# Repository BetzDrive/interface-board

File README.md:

# Interface Board

This board is intended to connect a chain of 48 VDC RS-485 motor controllers to
the outside world.

## Features

 * USB - RS485 conversion. This is accomplished via the [FT232H](https://www.ftdichip.com/Products/ICs/FT232H.htm) and [ADM2682E](https://www.analog.com/en/products/adm2682e.html)
 IC's. The combination of these chips should provide full electrical isolation
 to the USB host and allow ~10 Mbps throughput to/from RS485.

 * Input power sanitizing. A [LM5066](https://www.ti.com/product/LM5066)
 hotswap controller IC provides sane controlled voltage ramps when the device
 is hot-plugged, and cuts power to the system when it exceeds ~56 volts. An
 input TVS diode starts kicks in around 65 V.

 * Backdrive surge supressing. Sometimes when motors are aggressively
 backdriven by an external power source, significant voltages are generated
 "back" onto the motor bus. The board is equipped to detect this condition and
 dump power through a 10-ohm power resistor. Hysteresis and timing is provided
 by a STM32L071 microcontroller.

## Resources

 * [Schematics in PDF](hardware/blue_interface_board.pdf)
 * KiCAD design files are found in [`hardware`](hardware)
 * fabrication files for rev.A are found in [`hardware/fab`](hardware/fab)

## Renderings

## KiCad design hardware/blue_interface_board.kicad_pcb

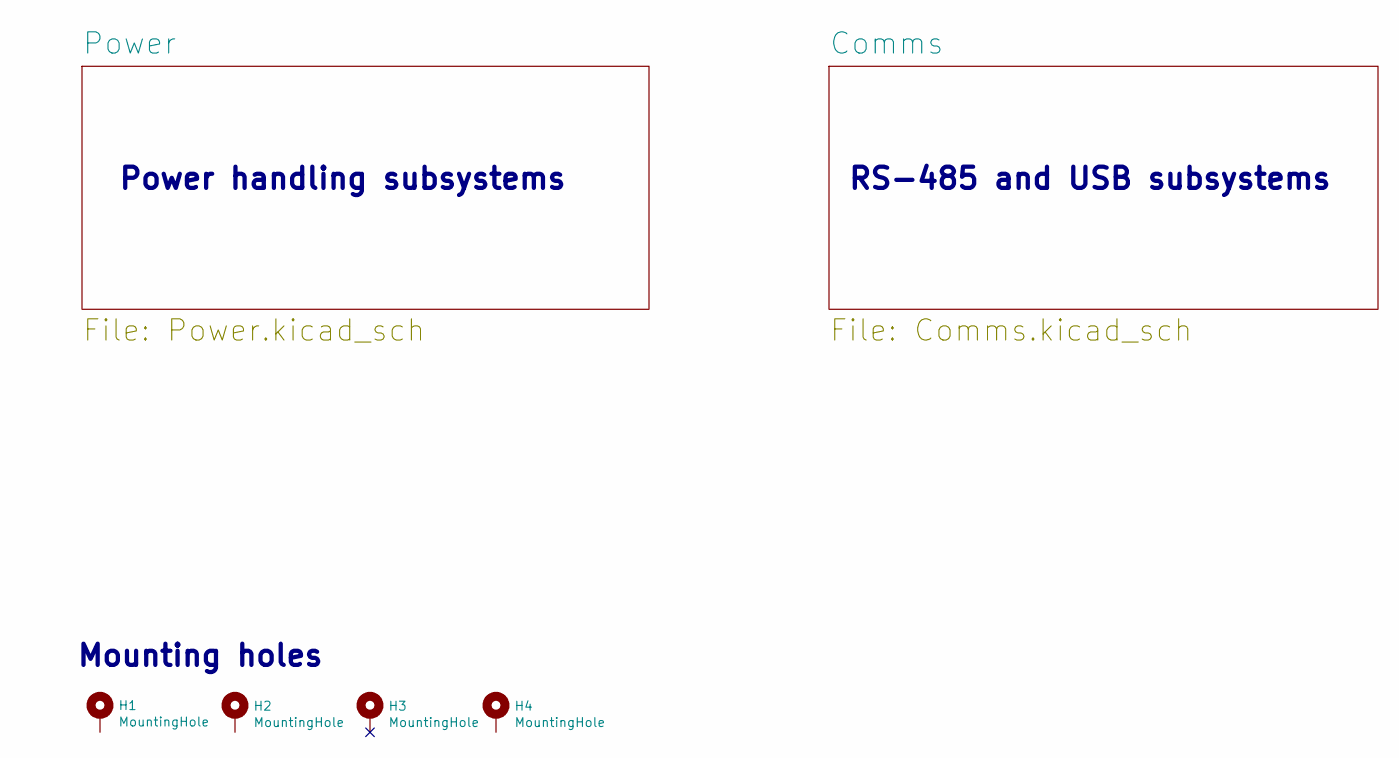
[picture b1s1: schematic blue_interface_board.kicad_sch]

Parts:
H1, H2, H3, H4: MountingHole; MountingHole_3.2mm_M3_DIN965_Pad

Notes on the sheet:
Mounting holes
Power handling subsystems
RS-485 and USB subsystems

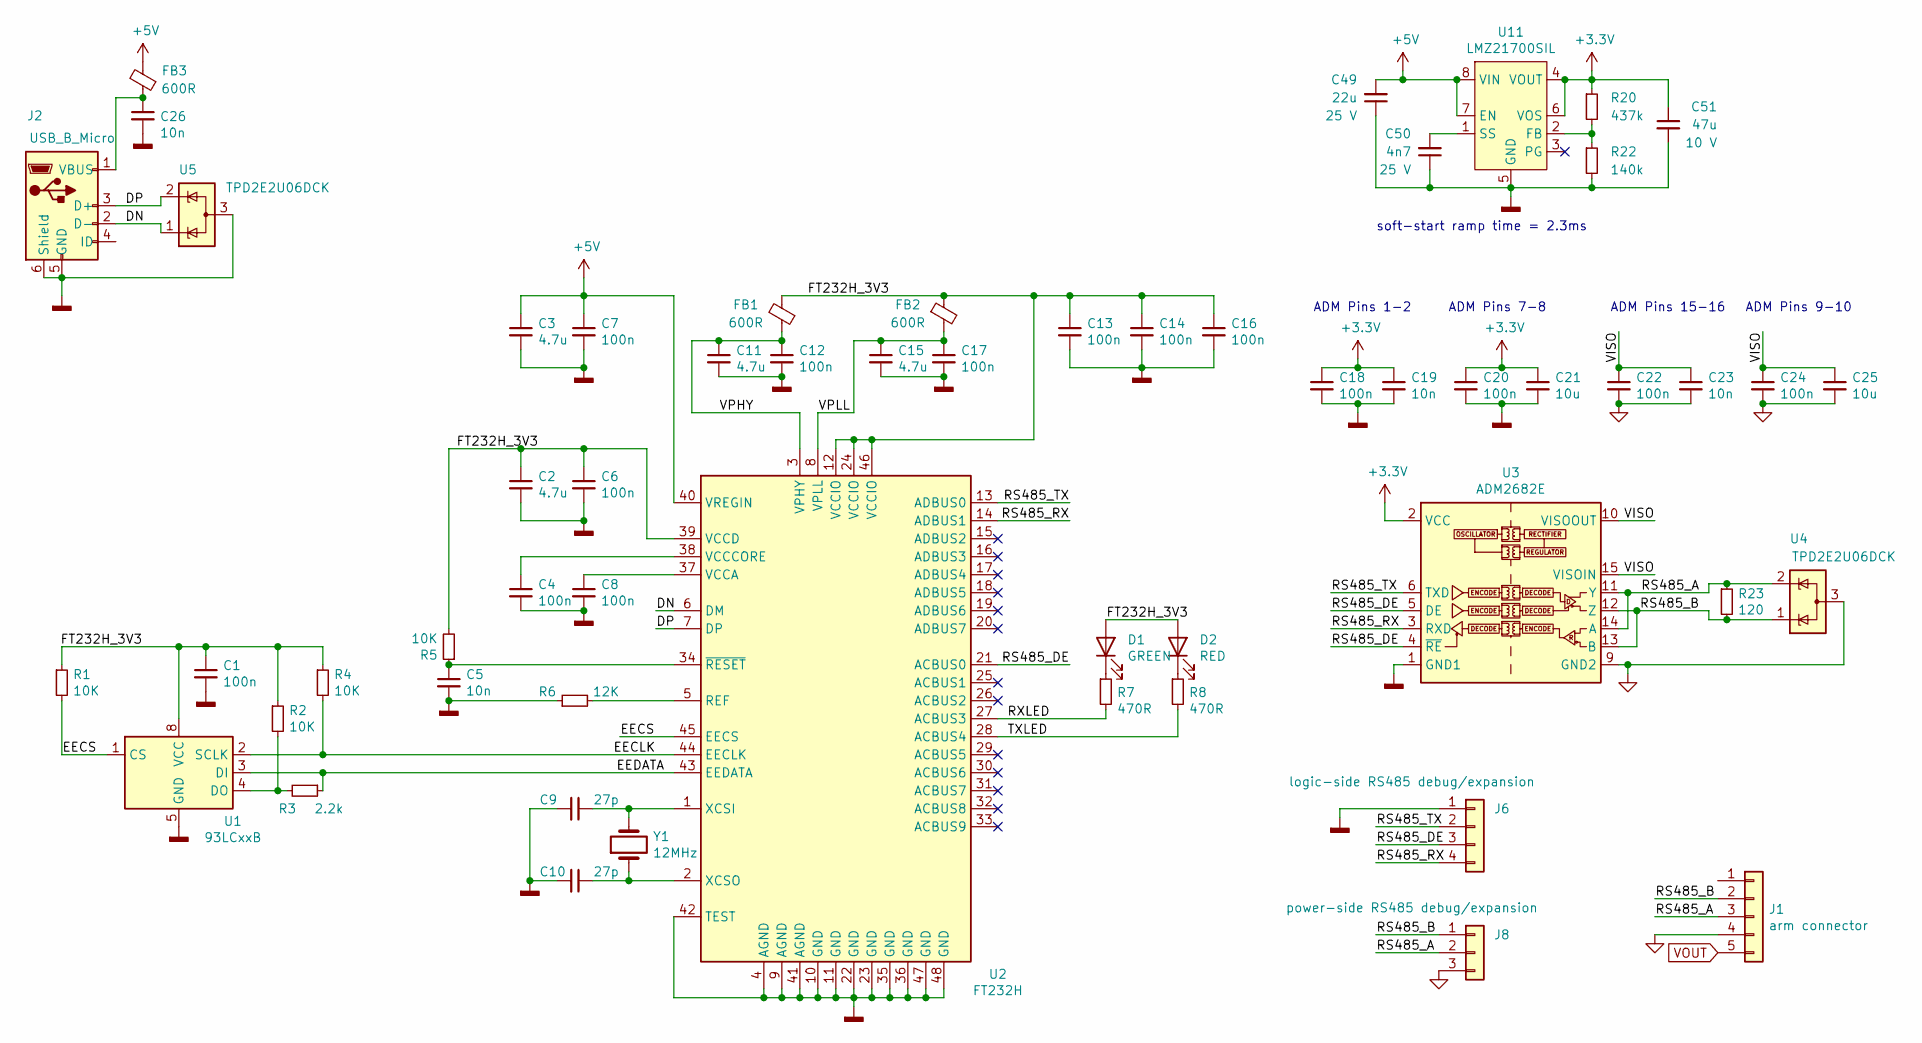
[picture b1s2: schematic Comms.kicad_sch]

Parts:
C1, C4, C6, C7, C8, C12, C13, C14, C16, C17, C18, C20, C22, C24: 100n; C_0603_1608Metric; MPN CC0603KRX7R9BB104
C2, C3, C11, C15: 4.7u; C_0603_1608Metric; Maximum Voltage 10 V; Tolerance 10%; MPN LMK107BJ475KA-T
C5, C19, C23, C26: 10n; C_0603_1608Metric; MPN CC0603KPX7R9BB103
C9, C10: 27p; C_0603_1608Metric; MPN CC0603JRNPO9BN270
C21, C25: 10u; C_0603_1608Metric; MPN GRM188R61A106KE69J
C49: 22u; C_1206_3216Metric; Maximum Voltage 25 V; Tolerance 10%; MPN CL31A226KAHNNNE
C50: 4n7; C_0603_1608Metric; Maximum Voltage 25 V; Tolerance 10%; MPN CC0603KRX7R0BB472
C51: 47u; C_1206_3216Metric; Maximum Voltage 10 V; Tolerance 10%; MPN GRM31CR61A476ME15L
D1: GREEN; LED_0603_1608Metric; MPN 150060VS75000
D2: RED; LED_0603_1608Metric; MPN 150060RS75000
FB1, FB2, FB3: 600R; R_0603_1608Metric; MPN 742792651
J1: arm connector; molex-436500511; MPN 436500510
J2: USB_B_Micro; USB_Micro-B_Wuerth_629105150521_CircularHoles; MPN 629105150521
J6: logic-side RS485 debug/expansion; PinHeader_1x04_P2.54mm_Vertical; MPN DNP
J8: power-side RS485 debug/expansion; PinHeader_1x03_P2.54mm_Vertical; MPN DNP
R1, R2, R4, R5: 10K; R_0603_1608Metric; MPN RC0603JR-0710KL
R3: 2.2k; R_0603_1608Metric; Tolerance 1%; MPN RC0603FR-072K2L
R6: 12K; R_0603_1608Metric; Tolerance 0.1%; MPN ERA-3AEB123V
R7, R8: 470R; R_0603_1608Metric; Tolerance 1%; MPN RC0603FR-07470RL
R20: 437k; R_0603_1608Metric; Tolerance 1%; MPN RC0603FR-07432KL
R22: 140k; R_0603_1608Metric; Tolerance 0.1%; MPN ERA-3AEB1403V
R23: 120; R_0603_1608Metric; Tolerance 1%; MPN RC0603FR-07120RL
U1: 93LCxxB; SOIC-8_3.9x4.9mm_P1.27mm; MPN 93LC56B/SN
U2: FT232H; LQFP-48_7x7mm_P0.5mm; MPN FT232HL-REEL
U3: ADM2682E; SOIC-16W_7.5x12.8mm_P1.27mm; MPN ADM2682EBRIZ
U4, U5: TPD2E2U06DCK; SOT-323_SC-70; MPN TPD2E2U06DCKR
U11: LMZ21700SIL; SIL0008E; MPN LMZ21700SILR
Y1: 12MHz; Crystal_SMD_5032-2Pin_5.0x3.2mm; MPN CX5032GB12000H0HPQZ1

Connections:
+3V3: C18.1, C19.1, C20.1, C21.1, C51.1, R20.1, U3.2 (VCC), U3.7 (VCC), U11.4 (VOUT), U11.6 (VOS)
+5V: C3.1, C7.1, C49.2, FB3.2, U2.40 (VREGIN), U11.7 (EN), U11.8 (VIN)
/Comms/DN: J2.2 (D-), U2.6 (DM), U5.1 (K)
/Comms/DP: J2.3 (D+), U2.7 (DP), U5.2 (K)
/Comms/EECLK: R4.2, U1.2 (SCLK), U2.44 (EECLK)
/Comms/EECS: R1.2, U1.1 (CS), U2.45 (EECS)
/Comms/EEDATA: R3.1, U1.3 (DI), U2.43 (EEDATA)
/Comms/FT232H_3V3: C1.1, C2.1, C6.1, C13.1, C14.1, C16.1, D1.2 (A), D2.2 (A), FB1.2, FB2.1, R1.1, R2.1, R4.1, R5.2, U1.8 (VCC), U2.12 (VCCIO), U2.24 (VCCIO), U2.39 (VCCD), U2.46 (VCCIO)
/Comms/RS485_A: J1.3, J8.2, R23.1, U3.11 (Y), U3.14 (A), U4.2 (K)
/Comms/RS485_B: J1.2, J8.1, R23.2, U3.12 (Z), U3.13 (B), U4.1 (K)
/Comms/RS485_DE: J6.3, U2.21 (ACBUS0), U3.4 (~RE), U3.5 (DE)
/Comms/RS485_RX: J6.4, U2.14 (ADBUS1), U3.3 (RXD)
/Comms/RS485_TX: J6.2, U2.13 (ADBUS0), U3.6 (TXD)
/Comms/RXLED: R7.2, U2.27 (ACBUS3)
/Comms/TXLED: R8.2, U2.28 (ACBUS4)
/Comms/VISO: C22.1, C23.1, C24.1, C25.1, U3.10 (VISOOUT), U3.15 (VISOIN)
/Comms/VPHY: C11.1, C12.1, FB1.1, U2.3 (VPHY)
/Comms/VPLL: C15.1, C17.1, FB2.2, U2.8 (VPLL)
GND: C22.2, C23.2, C24.2, C25.2, J1.4, J8.3, U3.9 (GND2), U3.16 (GND2), U4.3 (A); also elsewhere on the board
GNDD: C1.2, C2.2, C3.2, C4.2, C5.2, C6.2, C7.2, C8.2, C9.2, C10.2, C11.2, C12.2, C13.2, C14.2, C15.2, C16.2, C17.2, C18.2, C19.2, C20.2, C21.2, C26.2, C49.1, C50.1, C51.2, J2.5 (GND), J2.6 (Shield), J6.1, R6.1, R22.2, U1.5 (GND), U2.4 (AGND), U2.9 (AGND), U2.10 (GND), U2.11 (GND), U2.22 (GND), U2.23 (GND), U2.35 (GND), U2.36 (GND), U2.41 (AGND), U2.42 (TEST), U2.47 (GND), U2.48 (GND), U3.1 (GND1), U3.8 (GND1), U5.3 (A), U11.5 (GND), U11.9 (PAD)
unnamed: C4.1, U2.38 (VCCCORE)
unnamed: C5.1, R5.1, U2.34 (~RESET)
unnamed: C8.1, U2.37 (VCCA)
unnamed: C9.1, U2.1 (XCSI), Y1.2
unnamed: C10.1, U2.2 (XCSO), Y1.1
unnamed: C26.1, FB3.1, J2.1 (VBUS)
unnamed: C50.2, U11.1 (SS)
unnamed: D1.1 (K), R7.1
unnamed: D2.1 (K), R8.1
unnamed: R2.2, R3.2, U1.4 (DO)
unnamed: R6.2, U2.5 (REF)
unnamed: R20.2, R22.1, U11.2 (FB)
VOUT: J1.5; also elsewhere on the board

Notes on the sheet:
ADM Pins 1-2
soft-start ramp time = 2.3ms
ADM Pins 7-8
ADM Pins 15-16
ADM Pins 9-10

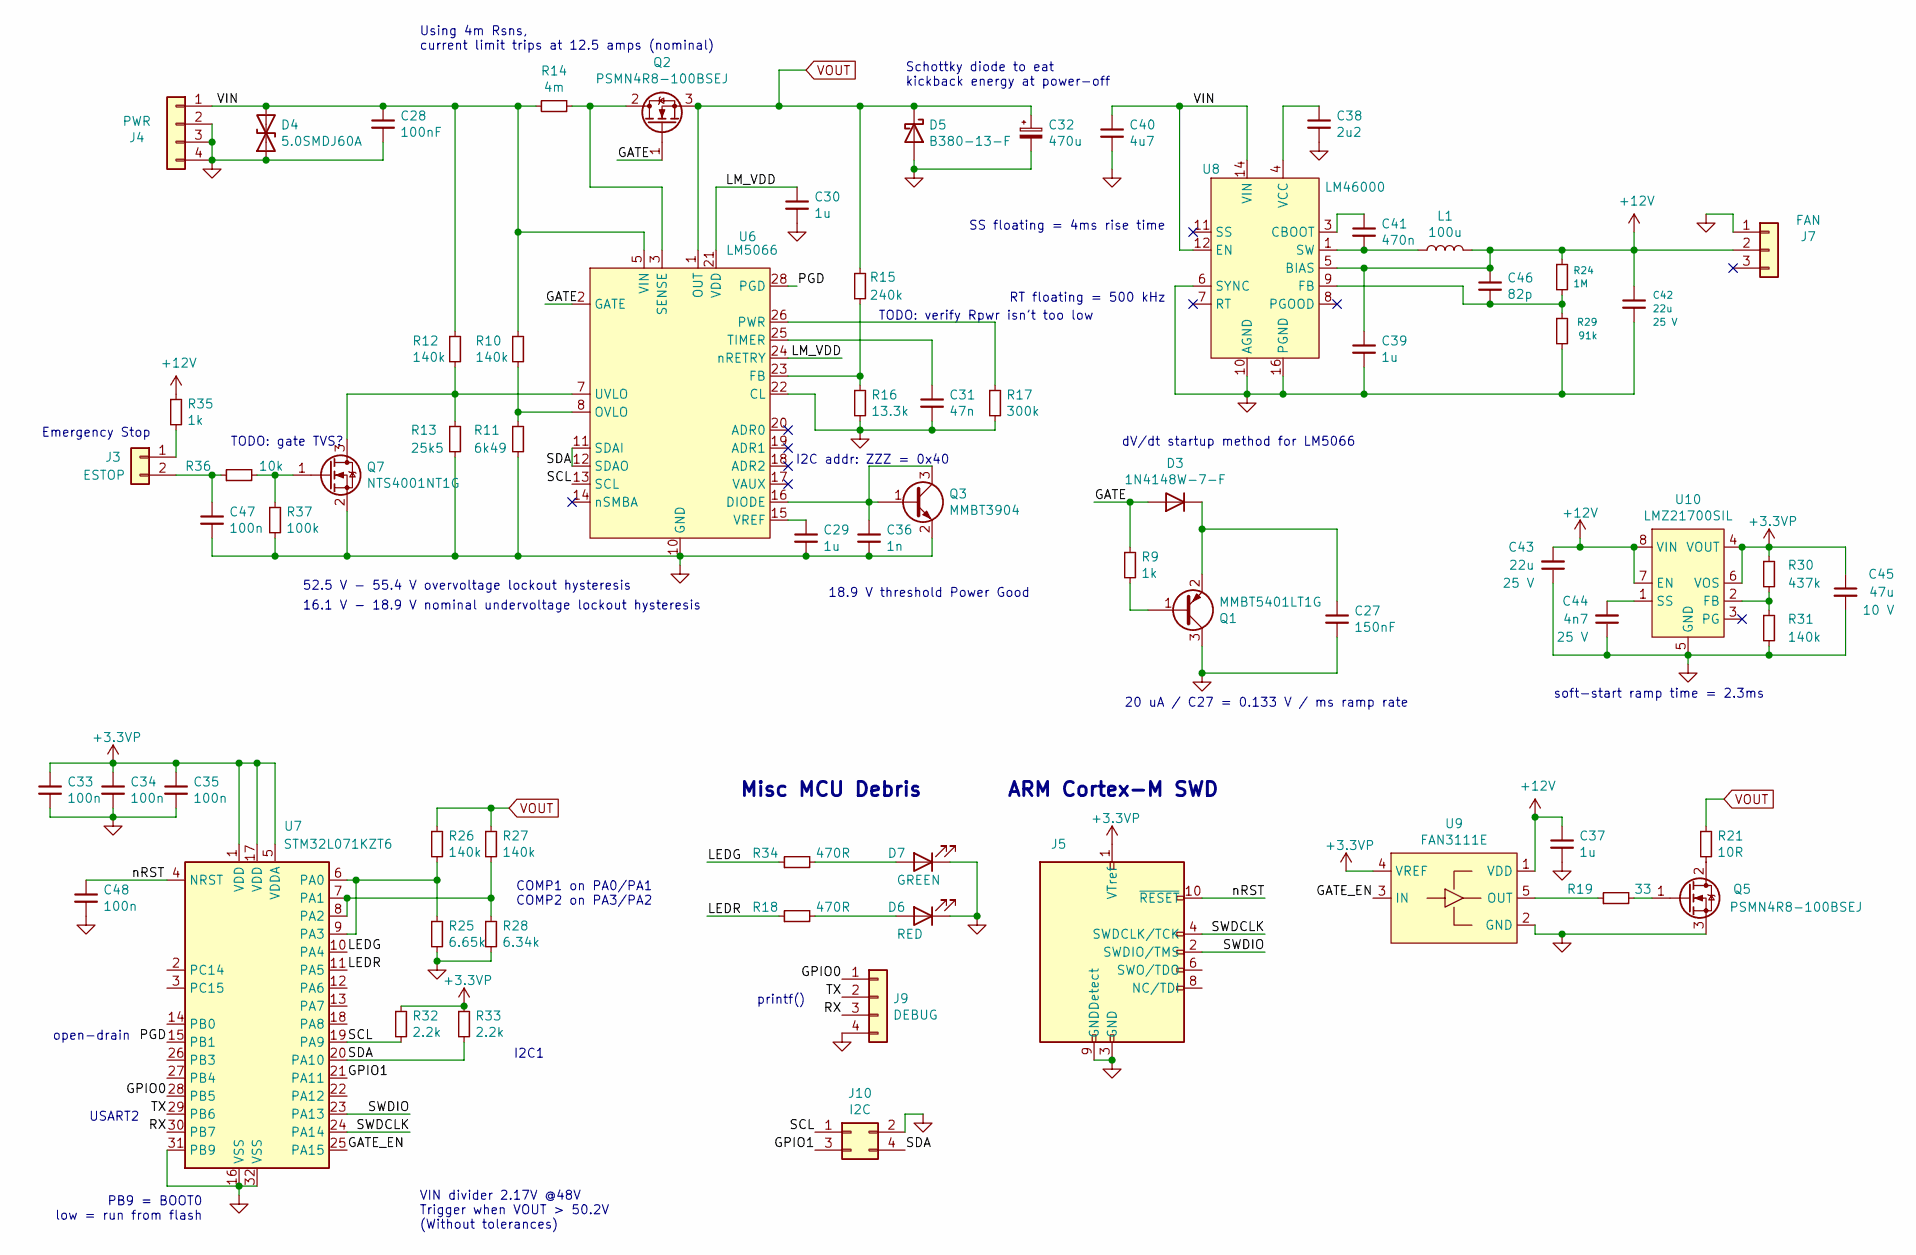
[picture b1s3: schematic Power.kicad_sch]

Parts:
C27: 150nF; C_1206_3216Metric; Maximum Voltage 250 V; Tolerance 10%; MPN C1206C154KARACAUTO
C28: 100nF; C_1206_3216Metric; Maximum Voltage 100 V; Tolerance 10%; MPN 12061C104KAT2A
C29, C30, C37, C39: 1u; C_0603_1608Metric; MPN CC0603KRX5R8BB105
C31: 47n; C_0603_1608Metric; MPN CL10B473JB8NNNC
C32: 470u; CP_Elec_18x17.5; Maximum Voltage 80 V; Tolerance 20%; MPN EEE-FK1K471AM
C33, C34, C35, C47, C48: 100n; C_0603_1608Metric; MPN CC0603KRX7R9BB104
C36: 1n; C_0603_1608Metric; MPN CC0603KRX7R9BB102
C38: 2u2; C_0603_1608Metric; Maximum Voltage 10 V; Tolerance 10%; MPN CC0603KRX5R6BB225
C40: 4u7; C_1206_3216Metric; Maximum Voltage 100 V; Tolerance 10%; MPN GRM31CC72A475KE11L
C41: 470n; C_0603_1608Metric; Maximum Voltage 25 V; Tolerance 10%; MPN CC0603KRX5R8BB474
C42, C43: 22u; C_1206_3216Metric; Maximum Voltage 25 V; Tolerance 10%; MPN CL31A226KAHNNNE
C44: 4n7; C_0603_1608Metric; Maximum Voltage 25 V; Tolerance 10%; MPN CC0603KRX7R0BB472
C45: 47u; C_1206_3216Metric; Maximum Voltage 10 V; Tolerance 10%; MPN GRM31CR61A476ME15L
C46: 82p; C_0603_1608Metric; Maximum Voltage 100 V; Tolerance 5%; MPN CL10C820JC81PNC
D3: 1N4148W-7-F; D_SOD-123; MPN 1N4148W-7-F
D4: 5.0SMDJ60A; D_SMC; MPN 5.0SMDJ60A
D5: B380-13-F; D_SMC; MPN B380-13-F
D6: RED; LED_0603_1608Metric; MPN 150060RS75000
D7: GREEN; LED_0603_1608Metric; MPN 150060VS75000
J3: ESTOP; Molex_Nano-Fit_105313-xx02_1x02_P2.50mm_Horizontal; MPN 1053131302
J4: PWR; molex-0436500213; MPN 436500214
J5: Conn_ARM_JTAG_SWD_10; PinHeader_2x05_P1.27mm_Vertical; MPN GRPB052VWVN-RC
J7: FAN; Molex_KK-254_AE-6410-03A_1x03_P2.54mm_Vertical; MPN 22232031
J9: DEBUG; PinHeader_1x04_P2.54mm_Vertical; MPN DNP
J10: I2C; PinHeader_2x02_P2.54mm_Vertical; MPN DNP
L1: 100u; L_7.3x7.3_H4.5; MPN 744777920
Q1: MMBT5401LT1G; SOT-23; MPN MMBT5401LT1G
Q2, Q5: PSMN4R8-100BSEJ; TO-263-2; MPN PSMN4R8-100BSEJ
Q3: MMBT3904; SOT-23; MPN MMBT3904-7-F
Q7: NTS4001NT1G; SOT-323_SC-70; MPN NTS4001NT1G
R9, R35: 1k; R_0603_1608Metric; Tolerance 1%; MPN RC0603FR-071KL
R10, R12, R26, R27, R31: 140k; R_0603_1608Metric; Tolerance 0.1%; MPN ERA-3AEB1403V
R11: 6k49; R_0603_1608Metric; Tolerance 0.1%; MPN ERA-3AEB6491V
R13: 25k5; R_0603_1608Metric; Tolerance 0.1%; MPN ERA-3AEB2552V
R14: 4m; R_2512_6332Metric; MPN WSL25124L000FEA18
R15: 240k; R_0603_1608Metric; Tolerance 0.1%; MPN ERA-3AEB244V
R16: 13.3k; R_0603_1608Metric; Tolerance 0.1%; MPN ERA-3AEB1332V
R17: 300k; R_0603_1608Metric; Tolerance 0.1%; MPN ERA-3AEB304V
R18, R34: 470R; R_0603_1608Metric; Tolerance 1%; MPN RC0603FR-07470RL
R19: 33; R_0603_1608Metric; Tolerance 1%; MPN RC0603FR-0733RL
R21: 10R; TO-247-2_Vertical; MPN PF2472-10RF1
R24: 1M; R_0603_1608Metric; Tolerance 1%; MPN RC0603FR-071ML
R25: 6.65k; R_0603_1608Metric; Tolerance 0.1%; MPN ERA-3AEB6651V
R28: 6.34k; R_0603_1608Metric; Tolerance 0.1%; MPN ERA-3AEB6341V
R29: 91k; R_0603_1608Metric; Tolerance 1%; MPN RC0402FR-0791KL
R30: 437k; R_0603_1608Metric; Tolerance 1%; MPN RC0603FR-07432KL
R32, R33: 2.2k; R_0603_1608Metric; Tolerance 1%; MPN RC0603FR-072K2L
R36: 10k; R_0603_1608Metric; MPN RC0603JR-0710KL
R37: 100k; R_0603_1608Metric; Tolerance 1%; MPN RC0603FR-07100KL
U6: LM5066; Texas_PWP0028A; MPN LM5066PMHX/NOPB
U7: STM32L071KZT6; LQFP-32_7x7mm_P0.8mm; MPN STM32L071KZT6
U8: LM46000; PWP0016G; MPN LM46000PWPR
U9: FAN3111E; SOT-23-5; MPN FAN3111ESX
U10: LMZ21700SIL; SIL0008E; MPN LMZ21700SILR

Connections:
+3.3VP: C33.1, C34.1, C35.1, C45.1, J5.1 (VTref), R30.1, R32.1, R33.1, U7.1 (VDD), U7.5 (VDDA), U7.17 (VDD), U9.4 (VREF), U10.4 (VOUT), U10.6 (VOS)
+12V: C37.1, C39.1, C42.1, C43.2, C46.1, J7.2, L1.2, R24.1, R35.1, U8.5 (BIAS), U9.1 (VDD), U10.7 (EN), U10.8 (VIN)
/Power/GATE: D3.2 (A), Q2.1 (G), R9.1, U6.2 (GATE)
/Power/GATE_EN: U7.25 (PA15), U9.3 (IN)
/Power/GPIO0: J9.1, U7.28 (PB5)
/Power/GPIO1: J10.3, U7.21 (PA11)
/Power/LEDG: R34.1, U7.10 (PA4)
/Power/LEDR: R18.1, U7.11 (PA5)
/Power/LM_VDD: C30.1, U6.21 (VDD), U6.24 (nRETRY)
/Power/PGD: U6.28 (PGD), U7.15 (PB1)
/Power/RX: J9.3, U7.30 (PB7)
/Power/SCL: J10.1, R32.2, U6.13 (SCL), U7.19 (PA9)
/Power/SDA: J10.4, R33.2, U6.11 (SDAI), U6.12 (SDAO), U7.20 (PA10)
/Power/SWDCLK: J5.4 (SWDCLK/TCK), U7.24 (PA14)
/Power/SWDIO: J5.2 (SWDIO/TMS), U7.23 (PA13)
/Power/TX: J9.2, U7.29 (PB6)
/Power/VIN: C28.1, C40.1, D4.2 (A2), J4.1, R10.1, R12.1, R14.2, U6.4 (VIN_K), U6.5 (VIN), U8.12 (EN), U8.13 (VIN), U8.14 (VIN)
/Power/nRST: C48.1, J5.10 (~RESET~), U7.4 (NRST)
GND: C27.2, C28.2, C29.2, C30.2, C31.2, C32.2, C33.2, C34.2, C35.2, C36.2, C37.2, C38.2, C39.2, C40.2, C42.2, C43.1, C44.1, C45.2, C47.2, C48.2, D4.1 (A1), D5.2 (A), D6.1 (K), D7.1 (K), J4.2, J4.3, J4.4, J5.3 (GND), J5.5 (GND), J5.9 (GNDDetect), J7.1, J9.4, J10.2, Q1.3 (C), Q3.2 (E), Q5.3 (S), Q7.2 (S), R11.2, R13.2, R16.2, R17.2, R25.2, R28.2, R29.2, R31.2, R37.2, U6.9 (AGND), U6.10 (GND), U6.22 (CL), U6.29 (GND), U7.16 (VSS), U7.31 (PB9), U7.32 (VSS), U8.6 (SYNC), U8.10 (AGND), U8.15 (PGND), U8.16 (PGND), U8.17 (AGND), U9.2 (GND), U10.5 (GND), U10.9 (PAD); also elsewhere on the board
unnamed: C27.1, D3.1 (K), Q1.2 (E)
unnamed: C29.1, U6.15 (VREF)
unnamed: C31.1, U6.25 (TIMER)
unnamed: C36.1, Q3.1 (B), Q3.3 (C), U6.16 (DIODE)
unnamed: C38.1, U8.4 (VCC)
unnamed: C41.1, U8.3 (CBOOT)
unnamed: C41.2, L1.1, U8.1 (SW), U8.2 (SW)
unnamed: C44.2, U10.1 (SS)
unnamed: C46.2, R24.2, R29.1, U8.9 (FB)
unnamed: C47.1, J3.2, R36.1
unnamed: D6.2 (A), R18.2
unnamed: D7.2 (A), R34.2
unnamed: J3.1, R35.2
unnamed: Q1.1 (B), R9.2
unnamed: Q2.2 (D), R14.1, U6.3 (SENSE)
unnamed: Q5.1 (G), R19.2
unnamed: Q5.2 (D), R21.2
unnamed: Q7.1 (G), R36.2, R37.1
unnamed: Q7.3 (D), R12.2, R13.1, U6.7 (UVLO)
unnamed: R10.2, R11.1, U6.8 (OVLO)
unnamed: R15.1, R16.1, U6.23 (FB)
unnamed: R17.1, U6.26 (PWR)
unnamed: R19.1, U9.5 (OUT)
unnamed: R25.1, R26.2, U7.6 (PA0), U7.9 (PA3)
unnamed: R27.2, R28.1, U7.7 (PA1), U7.8 (PA2)
unnamed: R30.2, R31.1, U10.2 (FB)
VOUT: C32.1, D5.1 (K), Q2.3 (S), R15.2, R21.1, R26.1, R27.1, U6.1 (OUT); also elsewhere on the board

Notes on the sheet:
Emergency Stop
open-drain
USART2
PB9 = BOOT0 low = run from flash
TODO: gate TVS?
52.5 V - 55.4 V overvoltage lockout hysteresis
16.1 V - 18.9 V nominal undervoltage lockout hysteresis
Using 4m Rsns, current limit trips at 12.5 amps (nominal)
VIN divider 2.17V @48V Trigger when VOUT > 50.2V (Without tolerances)
I2C1
COMP1 on PA0/PA1 COMP2 on PA3/PA2
printf()
18.9 V threshold Power Good
Schottky diode to eat kickback energy at power-off
Misc MCU Debris
I2C addr: ZZZ = 0x40
TODO: verify Rpwr isn't too low
dV/dt startup method for LM5066
SS floating = 4ms rise time
RT floating = 500 kHz
ARM Cortex-M SWD
20 uA / C27 = 0.133 V / ms ramp rate
soft-start ramp time = 2.3ms

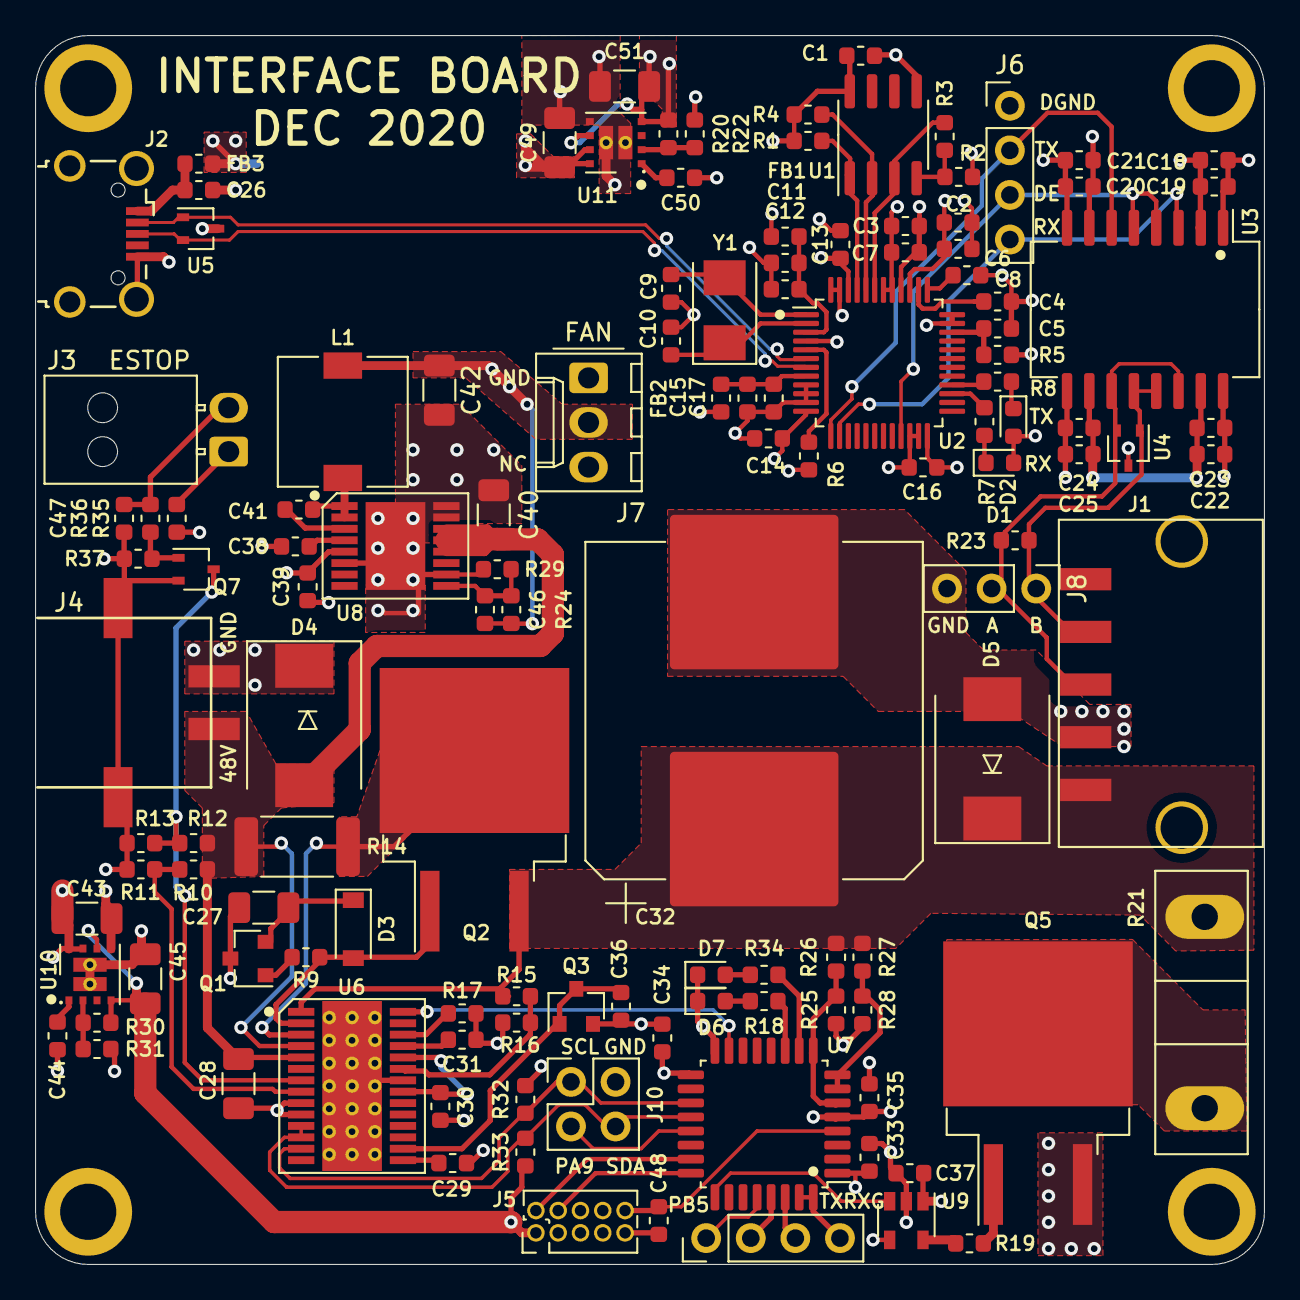
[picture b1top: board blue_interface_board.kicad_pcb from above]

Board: 4 copper layers, 70.0 x 70.0 mm, 130 parts (0 on the bottom side), 77 nets.

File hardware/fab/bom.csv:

Component,Quantity Per PCB,References,Value,Footprint,MFN,MPN,D1N,D1PN,Maximum Voltage,Tolerance
1,19,C1 C4 C6 C7 C8 C12 C13 C14 C16 C17 C18 C20 C22 C24 C33 C34 C35 C47 C48,100n,C_0603_1608Metric,Yageo,CC0603KRX7R9BB104,Digikey,311-1344-1-ND,,
2,1,C28,100nF,C_1206_3216Metric,AVX,12061C104KAT2A,Digikey,478-1529-1-ND,100 V,10%
3,4,C5 C19 C23 C26,10n,C_0603_1608Metric,Yageo,CC0603KPX7R9BB103,Digikey,311-1572-1-ND,,
4,2,C21 C25,10u,C_0603_1608Metric,Murata,GRM188R61A106KE69J,Digikey,490-14372-1-ND,,
5,1,C27,150nF,C_1206_3216Metric,KEMET,C1206C154KARACAUTO,Digikey,399-17949-1-ND,250 V,10%
6,1,C36,1n,C_0603_1608Metric,Yageo,CC0603KRX7R9BB102,Digikey,311-1080-1-ND,,
7,4,C29 C30 C37 C39,1u,C_0603_1608Metric,Yageo,CC0603KRX5R8BB105,Digikey,311-1445-1-ND,,
8,3,C42 C43 C49,22u,C_1206_3216Metric,Samsung,CL31A226KAHNNNE,Digikey,1276-3047-1-ND,25 V,10%
9,2,C9 C10,27p,C_0603_1608Metric,Yageo,CC0603JRNPO9BN270,Digikey,311-1063-1-ND,,
10,1,C38,2u2,C_0603_1608Metric,Yageo,CC0603KRX5R6BB225,Digikey,311-1451-1-ND,10 V,10%
11,4,C2 C3 C11 C15,4.7u,C_0603_1608Metric,Tayio Yuden,LMK107BJ475KA-T,Digikey,587-1441-1-ND,10 V,10%
12,1,C41,470n,C_0603_1608Metric,Yageo,CC0603KRX5R8BB474,Digikey,311-3365-1-ND,25 V,10%
13,1,C32,470u,CP_Elec_18x17.5,Panasonic,EEE-FK1K471AM,Digikey,PCE4859CT-ND,80 V,20%
14,1,C31,47n,C_0603_1608Metric,Samsung Electro-Mechanics,CL10B473JB8NNNC,Digikey,1276-2070-2-ND,,
15,2,C45 C51,47u,C_1206_3216Metric,Murata,GRM31CR61A476ME15L,Digikey,490-5528-1-ND,10 V,10%
16,2,C44 C50,4n7,C_0603_1608Metric,Yageo,CC0603KRX7R0BB472,Digikey,311-3366-1-ND,25 V,10%
17,1,C40,4u7,C_1206_3216Metric,Murata,GRM31CC72A475KE11L,Digikey,490-18620-1-ND,100 V,10%
18,1,C46,82p,C_0603_1608Metric,Samsung,CL10C820JC81PNC,Digikey,1276-2344-1-ND,100 V,5%
19,1,D3,1N4148W-7-F,D_SOD-123,Diodes Inc,1N4148W-7-F,Digikey,1N4148W-FDICT-ND,,
20,1,D4,5.0SMDJ60A,D_SMC,Bourns,5.0SMDJ60A,Digikey,5.0SMDJ60ABBCT-ND,,
21,1,D5,B380-13-F,D_SMC,Diodes Inc,B380-13-F,Digikey,B380-FDICT-ND,,
22,2,D1 D7,GREEN,LED_0603_1608Metric,Wurth,150060VS75000,Digikey,732-4980-1-ND,,
23,2,D2 D6,RED,LED_0603_1608Metric,Wurth,150060RS75000,Digikey,732-4978-1-ND,,
24,3,FB1 FB2 FB3,600R,R_0603_1608Metric,Wurth,742792651,Digikey,732-1593-1-ND,,
25,1,J5,Conn_ARM_JTAG_SWD_10,PinHeader_2x05_P1.27mm_Vertical,Sullins,GRPB052VWVN-RC,Digikey,S9015E-05-ND,,
26,1,J3,ESTOP,Molex_Nano-Fit_105313-xx02_1x02_P2.50mm_Horizontal,Molex,1053131302,Digikey,WM15141-ND,,
27,1,J7,FAN,Molex_KK-254_AE-6410-03A_1x03_P2.54mm_Vertical,Molex,22232031,Digikey,WM4201-ND,,
28,1,J10,I2C,PinHeader_2x02_P2.54mm_Vertical,DNP,DNP,DNP,DNP,,
29,1,J4,PWR,molex-0436500213,Molex,436500214,Digikey,WM14310CT-ND,,
30,1,J2,USB_B_Micro,USB_Micro-B_Wuerth_629105150521_CircularHoles,Wurth,629105150521,Digikey,732-5960-6-ND,,
31,1,J1,arm connector,molex-436500511,Molex,436500510,Digikey,WM1888CT-ND,,
32,2,J6 J9,logic-side RS485 debug/expansion,PinHeader_1x04_P2.54mm_Vertical,DNP,DNP,DNP,DNP,,
33,1,J8,power-side RS485 debug/expansion,PinHeader_1x03_P2.54mm_Vertical,DNP,DNP,DNP,DNP,,
34,1,L1,100u,L_7.3x7.3_H4.5,Wurth,744777920,Digikey,732-1199,,
35,1,Q3,MMBT3904,SOT-23,Diodes Inc,MMBT3904-7-F,Digikey,MMBT3904-FDICT-ND,,
36,1,Q1,MMBT5401LT1G,SOT-23,ON Semi,MMBT5401LT1G,Digikey,MMBT5401LT1GOSCT-ND,,
37,1,Q7,NTS4001NT1G,SOT-323_SC-70,ON Semi,NTS4001NT1G,Digikey,NTS4001NT1GOSTR-ND,,
38,2,Q2 Q5,PSMN4R8-100BSEJ,TO-263-2,NXP,PSMN4R8-100BSEJ,Digikey,1727-1103-1-ND,,
39,1,R37,100k,R_0603_1608Metric,Yageo,RC0603FR-07100KL,Digikey,311-100KHRCT-ND,,1%
40,5,R1 R2 R4 R5 R36,10K,R_0603_1608Metric,Yageo,RC0603JR-0710KL,Digikey,311-10KGRCT-ND,,
41,1,R21,10R,TO-247-2_Vertical,Riedon,PF2472-10RF1,Digikey,696-1107-5-ND,,
42,1,R23,120,R_0603_1608Metric,Yageo,RC0603FR-07120RL,Digikey,311-120HRCT-ND,,1%
43,1,R6,12K,R_0603_1608Metric,Panasonic,ERA-3AEB123V,Digikey,P12KDBCT-ND,,0.1%
44,1,R16,13.3k,R_0603_1608Metric,Panasonic,ERA-3AEB1332V,Digikey,P13.3KDBTR-ND,,0.1%
45,6,R10 R12 R22 R26 R27 R31,140k,R_0603_1608Metric,Panasonic,ERA-3AEB1403V,Digikey,P140KDBCT-ND,,0.1%
46,1,R24,1M,R_0603_1608Metric,Yageo,RC0603FR-071ML,Digikey,311-1.00MHRCT-ND,,1%
47,2,R9 R35,1k,R_0603_1608Metric,Yageo,RC0603FR-071KL,Digikey,311-1.00KHRCT-ND,,1%
48,3,R3 R32 R33,2.2k,R_0603_1608Metric,Yageo,RC0603FR-072K2L,Digikey,311-2.20KHRCT-ND,,1%
49,1,R15,240k,R_0603_1608Metric,Panasonic,ERA-3AEB244V,Digikey,P240KDBTR-ND,,0.1%
50,1,R13,25k5,R_0603_1608Metric,Panasonic,ERA-3AEB2552V,Digikey,P25.5KDBCT-ND,,0.1%
51,1,R17,300k,R_0603_1608Metric,Panasonic,ERA-3AEB304V,Digikey,P300KDBTR-ND,,0.1%
52,1,R19,33,R_0603_1608Metric,Yageo,RC0603FR-0733RL,Digikey,311-33.0HRCT-ND,,1%
53,2,R20 R30,437k,R_0603_1608Metric,Yageo,RC0603FR-07432KL,Digikey,311-432KHRCT-ND,,1%
54,4,R7 R8 R18 R34,470R,R_0603_1608Metric,Yageo,RC0603FR-07470RL,Digikey,311-470HRCT-ND,,1%
55,1,R14,4m,R_2512_6332Metric,Vishay Dale,WSL25124L000FEA18,Digikey,WSLH-.004TR-ND,,
56,1,R28,6.34k,R_0603_1608Metric,Panasonic,ERA-3AEB6341V,Digikey,P6.34KDBCT-ND,,0.1%
57,1,R25,6.65k,R_0603_1608Metric,Panasonic,ERA-3AEB6651V,Digikey,P6.65KDBCT-ND,,0.1%
58,1,R11,6k49,R_0603_1608Metric,Panasonic,ERA-3AEB6491V,Digikey,P6.49KDBCT-ND,,0.1%
59,1,R29,91k,R_0603_1608Metric,Yageo,RC0402FR-0791KL,Digikey,311-91.0KLRCT-ND,,1%
60,1,U1,93LCxxB,SOIC-8_3.9x4.9mm_P1.27mm,Microchip,93LC56B/SN,Digikey,93LC56B/SN-ND,,
61,1,U3,ADM2682E,SOIC-16W_7.5x12.8mm_P1.27mm,Analog Devices,ADM2682EBRIZ,Digikey,ADM2682EBRIZ-ND,,
62,1,U9,FAN3111E,SOT-23-5,ON Semi,FAN3111ESX,Digikey,FAN3111ESXCT-ND,,
63,1,U2,FT232H,LQFP-48_7x7mm_P0.5mm,FTDI,FT232HL-REEL,Digikey,768-1101-1-ND,,
64,1,U8,LM46000,PWP0016G,TI,LM46000PWPR,Digikey,296-40222-1-ND,,
65,1,U6,LM5066,Texas_PWP0028A,TI,LM5066PMHX/NOPB,Digikey,296-LM5066PMHX/NOPBCT-ND,,
66,2,U10 U11,LMZ21700SIL,SIL0008E,TI,LMZ21700SILR,Digikey,296-44325-1-ND,,
67,1,U7,STM32L071KZT6,LQFP-32_7x7mm_P0.8mm,ST,STM32L071KZT6,Digikey,497-18578-ND,,
68,2,U4 U5,TPD2E2U06DCK,SOT-323_SC-70,TI,TPD2E2U06DCKR,Digikey,296-TPD2E2U06DCKRDKR-ND,,
69,1,Y1,12MHz,Crystal_SMD_5032-2Pin_5.0x3.2mm,Kyocera,CX5032GB12000H0HPQZ1,Digikey,1253-1375-1-ND,,





Component Groups:,69
Component Count:,126
Fitted Components:,126
Number of PCBs:,1
Total components:,126
Schematic Version:,
Schematic Date:,
PCB Variant:,['default']
BoM Date:,Wed 02 Dec 2020 09:00:02 AM PST
Schematic Source:,blue_interface_board.kicad_sch
KiCad Version:,Eeschema 5.99.0-unknown-dd374e12a~102~ubuntu20.04.1

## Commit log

2019-07-11 First draft of schematic for interface board
    Includes following features:
    * Hotswap controller with TVS diodes for control of input spikes
    * Fully isolated RS485 driver (also protected by TVS diodes on the data lines)
    * USB high speed FTDI USB - RS485 controller, capable of bauds up to 12 MBps
2019-07-12 Added protection from motor regeneration through capacitors + MOSFET, started placement and routing
2019-07-19 WIP with component placement
2019-08-06 Finished schematic, placement and routing, only silkscreen TODO
2019-08-28 Fixed flipped connector, changed most placement
2019-11-18 Fix DRCs and minor improvements
2019-11-18 Silk screen and cosmetic fixes
2019-11-19 Changed voltage regulator, added I2C interface
2019-12-05 Changed connectors to microfit, added fan output
2019-12-05 Fixed power limit to avoid going into fault
2019-12-10 Reverted to nanofit for e-stop
2019-12-11 Changed USB connector to be on same side
2020-02-18 add rs485 termination, change to SOT-323 TVS diodes, various OCD
2020-02-19 working through the power subsystems now. changed e-stop topology.
2020-02-21 adding a few notes
2020-02-22 add two part numbers
2020-02-22 recalculate lm5066 passives
2020-02-22 fix Q3 pinout and chase a few part numbers
2020-02-24 WIP 48v-12v dc/dc converter tweaks. need to restore to BLDC values
2020-02-24 add MCU reset cap, tweak dc-dc feedback divider
2020-02-25 add part numbers, minor tweaks
2020-02-25 add MOSFET drive IC, simply a bit by pushing more into MCU, tweak layout
2020-02-25 Calculations for LM5066 values (incomplete)
2020-02-25 Adding motor capacitive load
2020-02-25 Redundant work (TI Spreadsheet more useful)
2020-02-25 layout tweaks. add debugging headers.
2020-02-26 ready to generate CAM
2020-02-26 CAM generation for rev A1 fab order
2020-02-26 commit schematics for convenience when writing firmware
2020-02-27 add renderings and some README
2020-02-27 repo restructuring, readme, and a tiny bit of documentation
2020-03-26 fixme
2020-03-26 add ft232h config file
2020-05-15 remove irrelevant fixme note
2020-09-06 Updating to new files and minor resistor fix
2020-09-06 Regen with resistor update
2020-10-18 Rsns to 5m (13A limit)
2020-10-18 Adding resistors for external divider (allows higher current sense)
2020-10-18 Adjusting timeout capacitor (1uF -> 52ms)
2020-10-18 Adjusting feedback resistors.
2020-10-18 Adding ERD resistors to layout.
2020-10-18 Revert "Adjusting timeout capacitor (1uF -> 52ms)"
    This reverts commit 7a30909a9925d87866bd3a766fa9658db1f002d2.
2020-10-18 Removing external resistor divider.
2020-10-18 Bumping Rpwr
2020-10-18 Adjusting Timer (C31)
2020-10-18 Updating info from schematic
2020-10-21 Adding second Power FET
2020-10-31 Revert "Adding second Power FET"
    This reverts commit e632f1e0367ea6556d8bc6e08f99c25e5b9f6e16.
2020-11-03 Power Bump to 530W+ (#3)
    * Rsns to 5m (13A limit)
    * Adding resistors for external divider (allows higher current sense)
    * Adjusting timeout capacitor (1uF -> 52ms)
    * Adjusting feedback resistors.
    * Adding ERD resistors to layout.
    * Revert "Adjusting timeout capacitor (1uF -> 52ms)"
2020-11-03 Updating BOM
2020-11-09 Adding STMCube submodule
2020-11-10 Initial work for power controller
2020-11-11 Initial Controller Firmware (#4)
    * Adding STMCube submodule
    * Initial work for power controller
2020-11-11 Create Workflow (#5)
    * Create main.yml
    * Update main.yml
    * Update main.yml
    * Update main.yml
    * Update main.yml
    * Update main.yml
2020-11-14 Add openocd config file
2020-11-14 Progress continued
2020-11-14 More make testing
2020-11-15 More testing
2020-11-17 Blink LED
2020-11-19 makefile target for flashing via Olimex adapter
2020-11-19 linker flags typo, also generate objdump and map file
2020-11-20 LED turns on! (Watchdog is tripping).
2020-11-20 Switching to HSI clock
2020-11-20 It's alive!
2020-11-20 Update to fix Disabled Command
2020-11-20 12V rail supplied off of VIN and Shunt EN switched to a clockable pin.
2020-11-20 Upload Debug (#6)
    * Add openocd config file
    * Progress continued
    * More make testing
    * More testing
    * Blink LED
    * makefile target for flashing via Olimex adapter
2020-11-20 Initial work towards configuring Shunt PWM
2020-11-25 Demo that the shunt enable works with just pin toggles
2020-11-25 25% duty cycle demo
2020-11-25 Clock Prescaler should be 0 otherwise every other tick skipped.
2020-11-25 Cleaning up and setting up ADC init (interrupts not triggering)
2020-11-27 DMA attempt
2020-11-27 Single conversion solution works.
2020-11-27 Correct startup procedure for ADC
2020-12-02 Updating all fab files
2020-12-02 Fixing PCB edges
2020-12-05 Updating date
2020-12-15 Fix component sizing mistake (0402 -> 0603)
2021-04-11 Create LICENSE
